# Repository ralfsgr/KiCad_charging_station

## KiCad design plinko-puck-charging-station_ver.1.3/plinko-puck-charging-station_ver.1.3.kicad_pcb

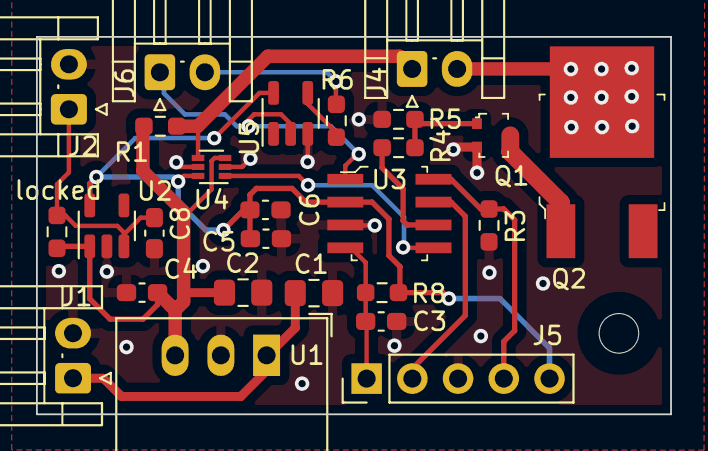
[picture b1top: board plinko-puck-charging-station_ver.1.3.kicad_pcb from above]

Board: 2 copper layers, 35.2 x 21.0 mm, 26 parts (0 on the bottom side), 17 nets.

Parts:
C1: 47uF; C_0805_2012Metric_Pad1.18x1.45mm_HandSolder
C2: 10uF; C_0805_2012Metric_Pad1.18x1.45mm_HandSolder
C3, C8: 0.1u; C_0603_1608Metric_Pad1.08x0.95mm_HandSolder
C4, C5, C6: 1uF; C_0603_1608Metric_Pad1.08x0.95mm_HandSolder
J1: Power_supply; JST_EH_S2B-EH_1x02_P2.50mm_Horizontal
J2: NC_push_button; JST_EH_S2B-EH_1x02_P2.50mm_Horizontal
J4: puck_contacts; JST_EH_S2B-EH_1x02_P2.50mm_Horizontal
J5: Conn_01x05; PinHeader_1x05_P2.54mm_Vertical
J6: LED; JST_EH_S2B-EH_1x02_P2.50mm_Horizontal
Q1: BSS214NWH6327XTSA1; SOT-323
Q2: CDCLD400 TR13; TO-252-3
R1: 0.06Ohm; R_0603_1608Metric_Pad0.98x0.95mm_HandSolder
R3, R5, R8: 10k; R_0603_1608Metric_Pad0.98x0.95mm_HandSolder
R4: 10; R_0603_1608Metric_Pad0.98x0.95mm_HandSolder
R6: 240; R_0603_1608Metric_Pad0.98x0.95mm_HandSolder
U1: SR05S7V2; Converter_DCDC_RECOM_R-78E-0.5_THT
U2: MCP1801T-3302I/OT; SOT-23-5
U3: STM32G031Jx; SOIC-8_W3.9mm
U4: INA185A4IDRLR; SOT-563
U5: SN74LVC1G14DBV; TSOT-23-5
locked: 10k; R_0603_1608Metric_Pad0.98x0.95mm_HandSolder

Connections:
3V3: C5.1, C6.1, J5.5, R8.1, U2.5 (Vout), U3.2 (VDD/VDDA), U4.6 (V+), U5.5 (VCC)
+7V2: C2.1, C4.1, R1.2, U1.3 (OUT), U2.1 (VIN), U4.3 (+), locked.1
GND: C1.2, C2.2, C3.2, C4.2, C5.2, C6.2, C8.2, J1.2, J2.2, J5.3, Q1.2 (S), R3.2, R5.1, U1.2 (GND), U2.2 (VSS), U3.3 (VSS/VSSA), U4.2 (GND), U4.5 (REF), U5.3 (GND)
LED: J6.1, U3.1 (OSC32_IN), U5.2
NRST: C3.1, J5.1, R8.2, U3.4 (PA0/NRST)
unnamed: C1.1, J1.1, U1.1 (IN)
unnamed: J4.1, R1.1, U4.4 (-)
unnamed: J6.2, R6.1
unnamed: Q1.1 (G), R4.2, R5.2
unnamed: R6.2, U5.4
PA8: U3.5 (PA8), U4.1
PA12: R4.1, U3.6 (PA12)
SHDN: C8.1, J2.1, U2.3 (SHDN), locked.2
SWCLK: J5.4, R3.1, U3.8 (BOOT0)
SWDIO: J5.2, U3.7 (PA13)
collector: Q1.3 (D), Q2.1 (G)
puck_GND_pogo_pin: J4.2, Q2.4 (D)

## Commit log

2025-03-01 upload
